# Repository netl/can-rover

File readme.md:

# can-rover

The goal is to convert cheap RC car kits in to computer driven robots by
replacing the receiver with a separate module.  
The project consists of three parts working as a whole:

1. [Hardware](#hardware)
2. [Firmware](#firmware)
3. [ROS2 node](#ros2-node)

## Hardware

features:

* XT60 passthrough
* fuse protected battery input
* battery current & voltage measurement
    * maximum rating: 20 V, 30 A
    * a charge current of 10 A max can be measured
* 2x canbus+power connectors
* 8 buffered servo channels
* 8 selectable addresses
* 8 buffered inputs with pull-up to 5V
* e-stop controlled servo power

### CAN header

Jumper for 120R termination.  
May be used to power low power stuff. Connector rated at 3 A.  

|pin|  signal |
|---|---------|
| 1 | GND     |
| 2 | Battery |
| 3 | CAN\_L  |
| 4 | CAN\_H  |

## Firmware

* can-utils: `sudo ip link set up can0 type can bitrate 500000`
* All messages are `big-endian`. 
* [python-can](https://python-can.readthedocs.io/en/stable/scripts.html) has great tools for debugging.
* build with `cd firmware; make`

### CAN messages

`base_address` is selectable by rotary switch. All messages have an offset from that address.
```c
uint8_t arbitration_id = base_address << 8; // address 0 would be: 0x000 and 7: 0x070
```

offset  |parameter       |I/O|bytes
--------|----------------|---|-----
0x0     | servo 1        | I | 1
...     | servo ...      | I | 1
0x7     | servo 8        | I | 1
0x8     | battery Voltage| O | 2
0x9     | battery Current| O | 2
0xa     | sensors 1 .. 8 | O | 1

### Servo

PWM in `1 µs` resolution and if channel hasn't been set within `1 s` it will default to `1500 µs`. For example: `servo 3` with `base_address = 5` would be set to `-90°` with:

```bash
$ cansend can0 052#3e8
```

### Battery monitor

Analog signals directly from A/D, maximum: `4095`

### Inputs

One byte where each bit represents an input

```c
bool value = inputs >> n-1 & 0x1;
```

## ROS2 node
Provided node bridges firmware to ros topics.

### Installation

1. Install [ROS2](https://docs.ros.org/en/jazzy/Installation.html)
2. create [ros2_ws](https://docs.ros.org/en/jazzy/Tutorials/Beginner-Client-Libraries/Creating-A-Workspace/Creating-A-Workspace.html)

```bash
apt install python3-rosdep python3-colcon-common-extensions
ln -s ros2_can_rover ~/ros2_ws/src/can_rover
cd ~/ros2_ws/
colcon build
source install/setup.bash
rosdep init
rosdep update
rosdep install --from-paths src -y --ignore-src
ros2 run can_rover can_rover
```

### Topics and parameters

Interfaces provided are bare minimum for simplicity

topic                      |type     |publish / subscribe|min   |max  |
---------------------------|---------|-------------------|------|-----|
`/rover/voltage`           |[Float32]|subscribe          |0   \*|20\* |
`/rover/current`           |[Float32]|subscribe          |-10 \*|30\* |
`/rover/watts`             |[Float32]|subscribe          |-200\*|600\*|
`/rover/wattHours`         |[Float32]|publish & subscribe|      |     |
`/rover/channel_<n>`       |[Float32]|publish            | -1   | 1   |
`/rover/input_<n>`         |[Bool]   |subscribe          | 0    | 1   |

*\*min/max values limited hardware tolerances and calibration*

parameter                  |type     |default   |
---------------------------|---------|----------|
`/rover/voltage_scale`     |[Float32]|20 / 2^12 |
`/rover/voltage_offset`    |[Float32]|0         |
`/rover/current_scale`     |[Float32]|-40 / 2^12|
`/rover/current_offset`    |[Float32]|10        |
`/rover/channel_<n>_scale` |[Float32]|500       |
`/rover/channel_<n>_offset`|[Float32]|1500      |

[Float32]:https://github.com/ros2/example_interfaces/blob/master/msg/Float32.msg
[Bool]:https://github.com/ros2/example_interfaces/blob/master/msg/Bool.msg

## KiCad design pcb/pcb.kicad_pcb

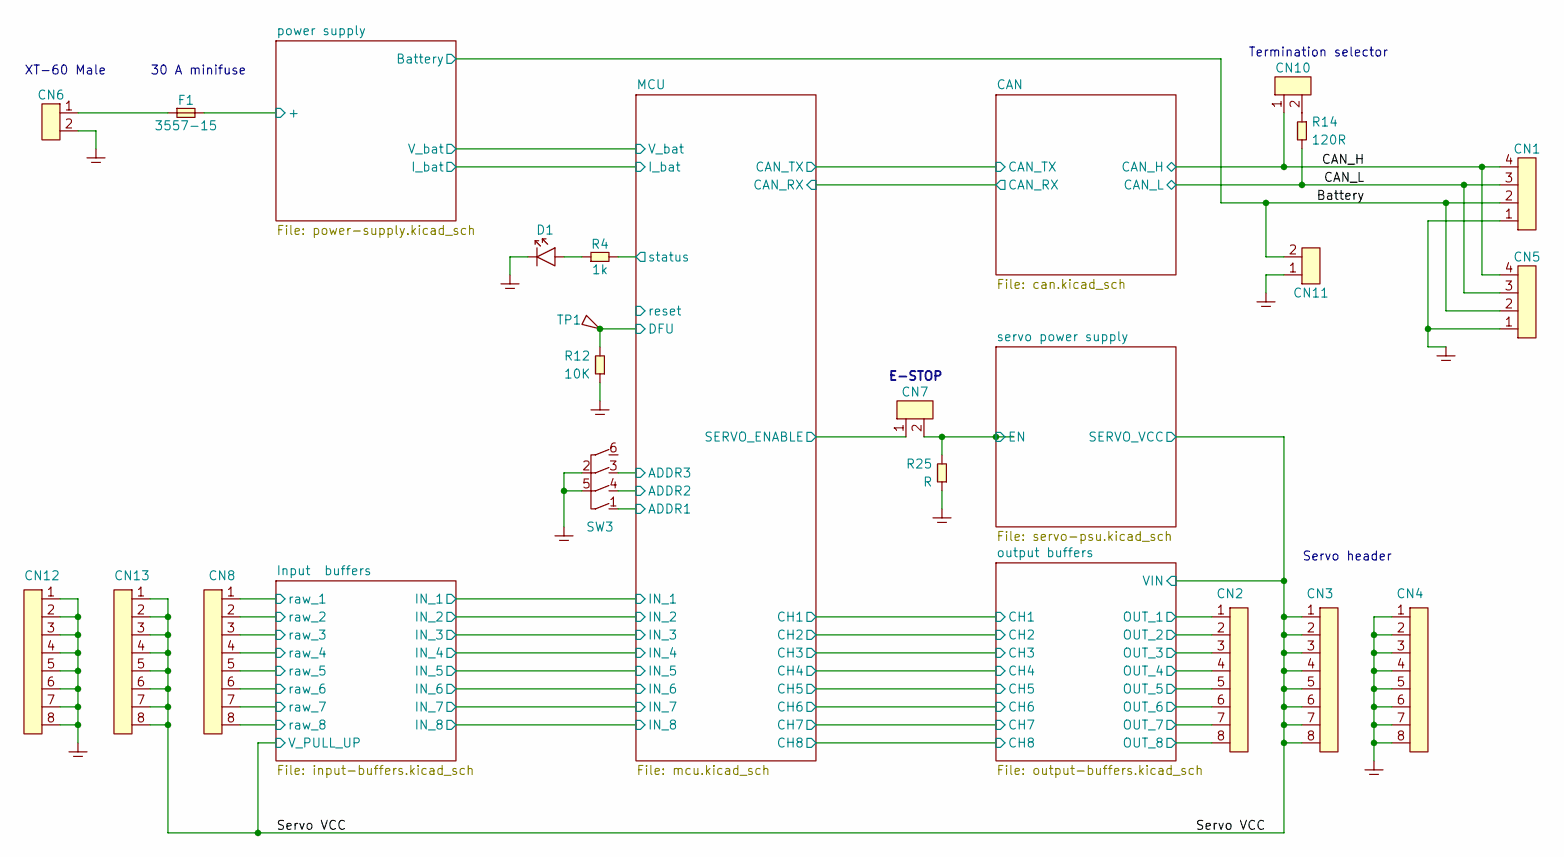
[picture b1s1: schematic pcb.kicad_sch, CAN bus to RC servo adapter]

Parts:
CN1, CN5: 1x4; jst-xh-4; MPN B4B-XH-A; DigiKey 455-B4B-XH-A-ND
CN2, CN3, CN4, CN8, CN12, CN13: 1x8
CN6, CN11: 1x2; XT60
CN7, CN10: 1x2
D1: LED; 0603
F1: F; 3557-15; MPN 3557-15; DigiKey 36-3557-15-ND
R4: 1k; 0603
R12: 10K; 0603
R14: 120R; 0603
R25: R; 0603
SW3: RD10RA8RTT; MPN RD10RA8RTT; Digi-Key 2449-RD10RA8RTT-ND
TP1: test_point

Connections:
/Battery: CN1.2, CN5.2, CN11.2; also elsewhere on the board
/CAN_H: CN1.4, CN5.4, CN10.1; also elsewhere on the board
/CAN_L: CN1.3, CN5.3, R14.2; also elsewhere on the board
/Input buffers/raw_1: CN8.1; also elsewhere on the board
/Input buffers/raw_2: CN8.2; also elsewhere on the board
/Input buffers/raw_3: CN8.3; also elsewhere on the board
/Input buffers/raw_4: CN8.4; also elsewhere on the board
/Input buffers/raw_5: CN8.5; also elsewhere on the board
/Input buffers/raw_6: CN8.6; also elsewhere on the board
/Input buffers/raw_7: CN8.7; also elsewhere on the board
/Input buffers/raw_8: CN8.8; also elsewhere on the board
/MCU/ADDR1: SW3.1; also elsewhere on the board
/MCU/ADDR2: SW3.4; also elsewhere on the board
/MCU/ADDR3: SW3.3; also elsewhere on the board
/MCU/DFU: R12.2, TP1.1 (TP); also elsewhere on the board
/MCU/SERVO_ENABLE: CN7.1; also elsewhere on the board
/MCU/status: R4.2; also elsewhere on the board
/Servo VCC: CN3.1, CN3.2, CN3.3, CN3.4, CN3.5, CN3.6, CN3.7, CN3.8, CN13.1, CN13.2, CN13.3, CN13.4, CN13.5, CN13.6, CN13.7, CN13.8; also elsewhere on the board
/output buffers/OUT_1: CN2.1; also elsewhere on the board
/output buffers/OUT_2: CN2.2; also elsewhere on the board
/output buffers/OUT_3: CN2.3; also elsewhere on the board
/output buffers/OUT_4: CN2.4; also elsewhere on the board
/output buffers/OUT_5: CN2.5; also elsewhere on the board
/output buffers/OUT_6: CN2.6; also elsewhere on the board
/output buffers/OUT_7: CN2.7; also elsewhere on the board
/output buffers/OUT_8: CN2.8; also elsewhere on the board
/power supply/+: F1.2; also elsewhere on the board
/servo power supply/EN: CN7.2, R25.2; also elsewhere on the board
GND: CN1.1, CN4.1, CN4.2, CN4.3, CN4.4, CN4.5, CN4.6, CN4.7, CN4.8, CN5.1, CN6.2, CN11.1, CN12.1, CN12.2, CN12.3, CN12.4, CN12.5, CN12.6, CN12.7, CN12.8, D1.2 (K), R12.1, R25.1, SW3.2, SW3.5; also elsewhere on the board
unnamed: CN6.1, F1.1
unnamed: CN10.2, R14.1
unnamed: D1.1 (A), R4.1

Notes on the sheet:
30 A minifuse
E-STOP
Termination selector
Servo header
XT-60 Male

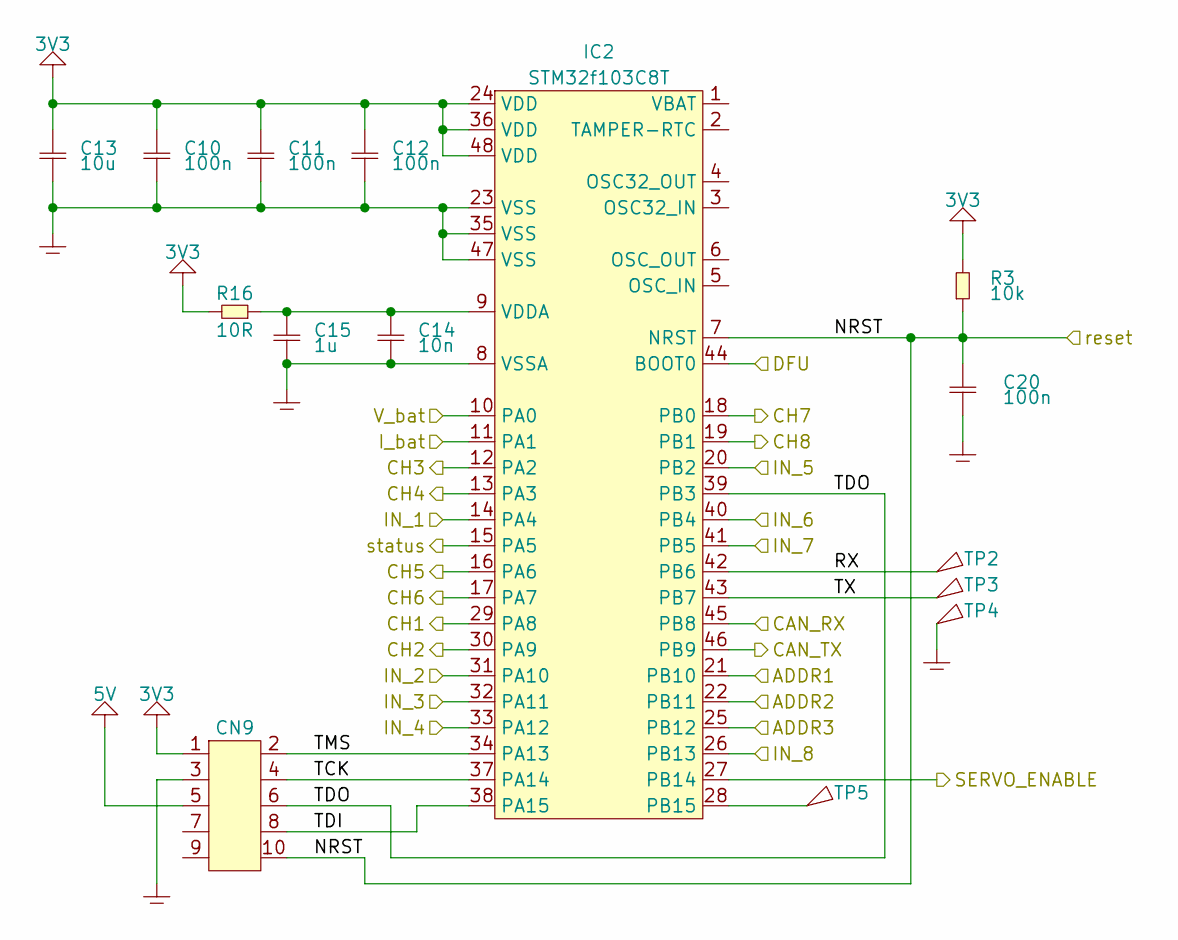
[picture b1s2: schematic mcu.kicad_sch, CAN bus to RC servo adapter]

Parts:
C10, C11, C12, C20: 100n; 0603
C13: 10u; 0603
C14: 10n; 0603
C15: 1u; 0603
CN9: 2x5; 2x5_test_points
IC2: STM32f103C8T; LQFP-48; MPN STM32F103C8T6TR; DigiKey 497-17666-1-ND
R3: 10k; 0603
R16: 10R; 0603
TP2, TP3, TP4, TP5: test_point

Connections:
3V3: C10.1, C11.1, C12.1, C13.1, CN9.1, IC2.24 (VDD), IC2.36 (VDD), IC2.48 (VDD), R3.2, R16.2; also elsewhere on the board
5V: CN9.5; also elsewhere on the board
/CAN/CAN_RX: IC2.45 (PB8); also elsewhere on the board
/CAN/CAN_TX: IC2.46 (PB9); also elsewhere on the board
/Input buffers/IN_1: IC2.14 (PA4); also elsewhere on the board
/Input buffers/IN_2: IC2.31 (PA10); also elsewhere on the board
/Input buffers/IN_3: IC2.32 (PA11); also elsewhere on the board
/Input buffers/IN_4: IC2.33 (PA12); also elsewhere on the board
/Input buffers/IN_5: IC2.20 (PB2); also elsewhere on the board
/Input buffers/IN_6: IC2.40 (PB4); also elsewhere on the board
/Input buffers/IN_7: IC2.41 (PB5); also elsewhere on the board
/Input buffers/IN_8: IC2.26 (PB13); also elsewhere on the board
/MCU/ADDR1: IC2.21 (PB10); also elsewhere on the board
/MCU/ADDR2: IC2.22 (PB11); also elsewhere on the board
/MCU/ADDR3: IC2.25 (PB12); also elsewhere on the board
/MCU/CH1: IC2.29 (PA8); also elsewhere on the board
/MCU/CH2: IC2.30 (PA9); also elsewhere on the board
/MCU/CH3: IC2.12 (PA2); also elsewhere on the board
/MCU/CH4: IC2.13 (PA3); also elsewhere on the board
/MCU/CH5: IC2.16 (PA6); also elsewhere on the board
/MCU/CH6: IC2.17 (PA7); also elsewhere on the board
/MCU/CH7: IC2.18 (PB0); also elsewhere on the board
/MCU/CH8: IC2.19 (PB1); also elsewhere on the board
/MCU/DFU: IC2.44 (BOOT0); also elsewhere on the board
/MCU/I_bat: IC2.11 (PA1); also elsewhere on the board
/MCU/NRST: C20.1, CN9.10, IC2.7 (NRST), R3.1
/MCU/RX: IC2.42 (PB6), TP2.1 (TP)
/MCU/SERVO_ENABLE: IC2.27 (PB14); also elsewhere on the board
/MCU/TCK: CN9.4, IC2.37 (PA14)
/MCU/TDI: CN9.8, IC2.38 (PA15)
/MCU/TDO: CN9.6, IC2.39 (PB3)
/MCU/TMS: CN9.2, IC2.34 (PA13)
/MCU/TX: IC2.43 (PB7), TP3.1 (TP)
/MCU/V_bat: IC2.10 (PA0); also elsewhere on the board
/MCU/status: IC2.15 (PA5); also elsewhere on the board
GND: C10.2, C11.2, C12.2, C13.2, C14.2, C15.2, C20.2, CN9.3, IC2.8 (VSSA), IC2.23 (VSS), IC2.35 (VSS), IC2.47 (VSS), TP4.1 (TP); also elsewhere on the board
unnamed: IC2.28 (PB15), TP5.1 (TP)
unnamed: C14.1, C15.1, IC2.9 (VDDA), R16.1

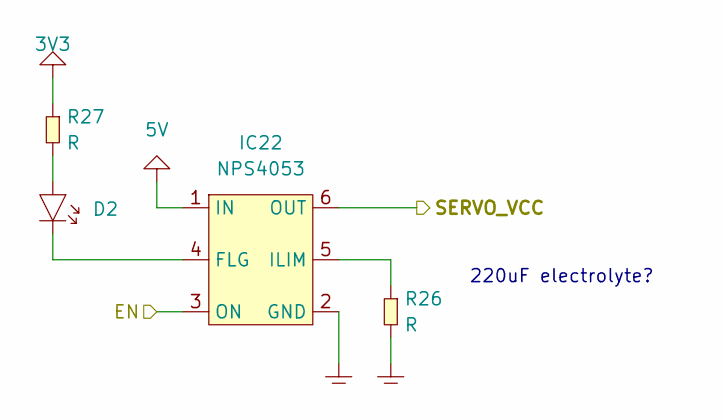
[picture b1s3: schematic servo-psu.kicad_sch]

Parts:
D2: LED; 0603
IC22: NPS4053; SOT-23-6; MPN NPS4053GVH; DigiKey 1727-NPS4053GVHCT-ND
R26, R27: R; 0603

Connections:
3V3: R27.1; also elsewhere on the board
5V: IC22.1 (IN); also elsewhere on the board
/Servo VCC: IC22.6 (OUT); also elsewhere on the board
/servo power supply/EN: IC22.3 (ON); also elsewhere on the board
GND: IC22.2 (GND), R26.2; also elsewhere on the board
unnamed: D2.1 (A), R27.2
unnamed: D2.2 (K), IC22.4 (FLG)
unnamed: IC22.5 (ILIM), R26.1

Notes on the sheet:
220uF electrolyte?

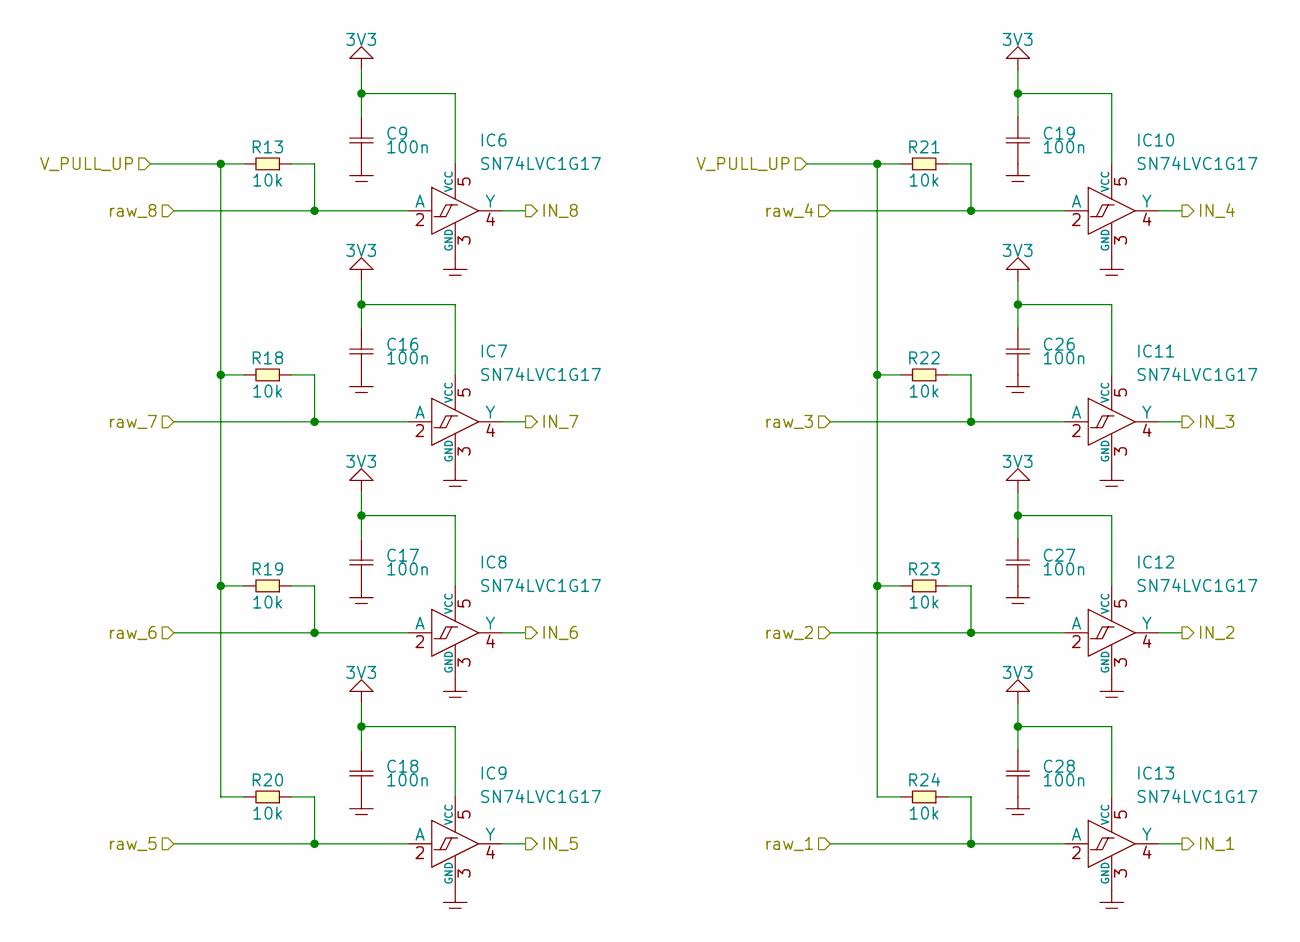
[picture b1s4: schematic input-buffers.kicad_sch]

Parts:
C9, C16, C17, C18, C19, C26, C27, C28: 100n; 0603
IC6, IC7, IC8, IC9, IC10, IC11, IC12, IC13: SN74LVC1G17; SC70-5L
R13, R18, R19, R20, R21, R22, R23, R24: 10k; 0603

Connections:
3V3: C9.2, C16.2, C17.2, C18.2, C19.2, C26.2, C27.2, C28.2, IC6.5 (VCC), IC7.5 (VCC), IC8.5 (VCC), IC9.5 (VCC), IC10.5 (VCC), IC11.5 (VCC), IC12.5 (VCC), IC13.5 (VCC); also elsewhere on the board
/Input buffers/IN_1: IC13.4 (Y); also elsewhere on the board
/Input buffers/IN_2: IC12.4 (Y); also elsewhere on the board
/Input buffers/IN_3: IC11.4 (Y); also elsewhere on the board
/Input buffers/IN_4: IC10.4 (Y); also elsewhere on the board
/Input buffers/IN_5: IC9.4 (Y); also elsewhere on the board
/Input buffers/IN_6: IC8.4 (Y); also elsewhere on the board
/Input buffers/IN_7: IC7.4 (Y); also elsewhere on the board
/Input buffers/IN_8: IC6.4 (Y); also elsewhere on the board
/Input buffers/raw_1: IC13.2 (A), R24.1; also elsewhere on the board
/Input buffers/raw_2: IC12.2 (A), R23.1; also elsewhere on the board
/Input buffers/raw_3: IC11.2 (A), R22.1; also elsewhere on the board
/Input buffers/raw_4: IC10.2 (A), R21.1; also elsewhere on the board
/Input buffers/raw_5: IC9.2 (A), R20.1; also elsewhere on the board
/Input buffers/raw_6: IC8.2 (A), R19.1; also elsewhere on the board
/Input buffers/raw_7: IC7.2 (A), R18.1; also elsewhere on the board
/Input buffers/raw_8: IC6.2 (A), R13.1; also elsewhere on the board
/Servo VCC: R13.2, R18.2, R19.2, R20.2, R21.2, R22.2, R23.2, R24.2; also elsewhere on the board
GND: C9.1, C16.1, C17.1, C18.1, C19.1, C26.1, C27.1, C28.1, IC6.3 (GND), IC7.3 (GND), IC8.3 (GND), IC9.3 (GND), IC10.3 (GND), IC11.3 (GND), IC12.3 (GND), IC13.3 (GND); also elsewhere on the board

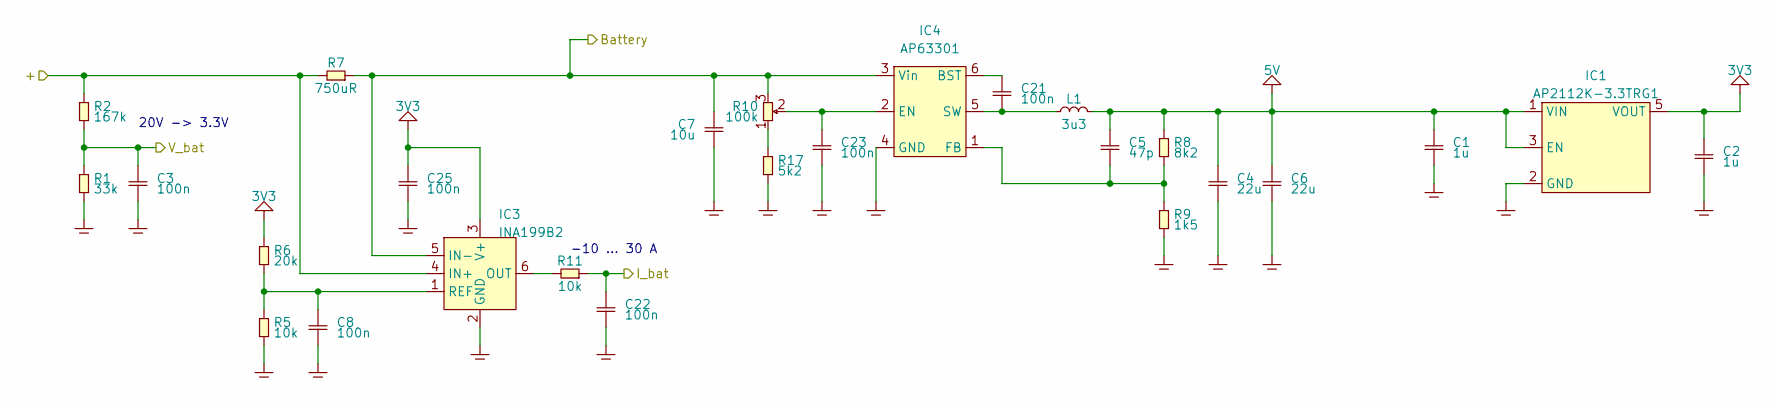
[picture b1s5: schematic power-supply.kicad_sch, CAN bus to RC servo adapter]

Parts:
C1, C2: 1u; 0603
C3, C8, C21, C22, C23, C25: 100n; 0603
C4, C6: 22u; 0603
C5: 47p; 0603
C7: 10u; 0603
IC1: AP2112K-3.3TRG1; SOT-23-5; MPN AP2112K-3.3TRG1; Digi-Key AP2112K-3.3TRG1DICT-ND
IC3: INA199B2; SC70-6L; MPN INA199B2DCKR; DigiKey 296-40119-1-ND
IC4: AP63301; TSOT-26; MPN AP63301WU-7; DigiKey 31-AP63301WU-7CT-ND
L1: 3u3; 5x5; MPN VLS5045EX-3R3N; DigiKey 445-174398-1-ND
R1: 33k; 0603
R2: 167k; 0603
R5, R11: 10k; 0603
R6: 20k; 0603
R7: 750uR; 2512-high-current
R8: 8k2; 0603
R9: 1k5; 0603
R10: 100k; 3362P; MPN 3362P-1-104LF; DigiKey 3362P-104LF-ND
R17: 5k2; 0603

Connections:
3V3: C2.1, C25.1, IC1.5 (VOUT), IC3.3 (V+), R6.2; also elsewhere on the board
5V: C1.1, C4.1, C5.1, C6.1, IC1.1 (VIN), IC1.3 (EN), L1.2, R8.2; also elsewhere on the board
/Battery: C7.1, IC3.5 (IN-), IC4.3 (Vin), R7.1, R10.3; also elsewhere on the board
/MCU/I_bat: C22.1, R11.1; also elsewhere on the board
/MCU/V_bat: C3.1, R1.2, R2.1; also elsewhere on the board
/power supply/+: IC3.4 (IN+), R2.2, R7.2; also elsewhere on the board
GND: C1.2, C2.2, C3.2, C4.2, C6.2, C7.2, C8.2, C22.2, C23.2, C25.2, IC1.2 (GND), IC3.2 (GND), IC4.4 (GND), R1.1, R5.1, R9.1, R17.1; also elsewhere on the board
unnamed: IC3.6 (OUT), R11.2
unnamed: C8.1, IC3.1 (REF), R5.2, R6.1
unnamed: C21.1, IC4.6 (BST)
unnamed: C23.1, IC4.2 (EN), R10.2
unnamed: C5.2, IC4.1 (FB), R8.1, R9.2
unnamed: C21.2, IC4.5 (SW), L1.1
unnamed: R10.1, R17.2

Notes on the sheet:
-10 ... 30 A
20V -> 3.3V

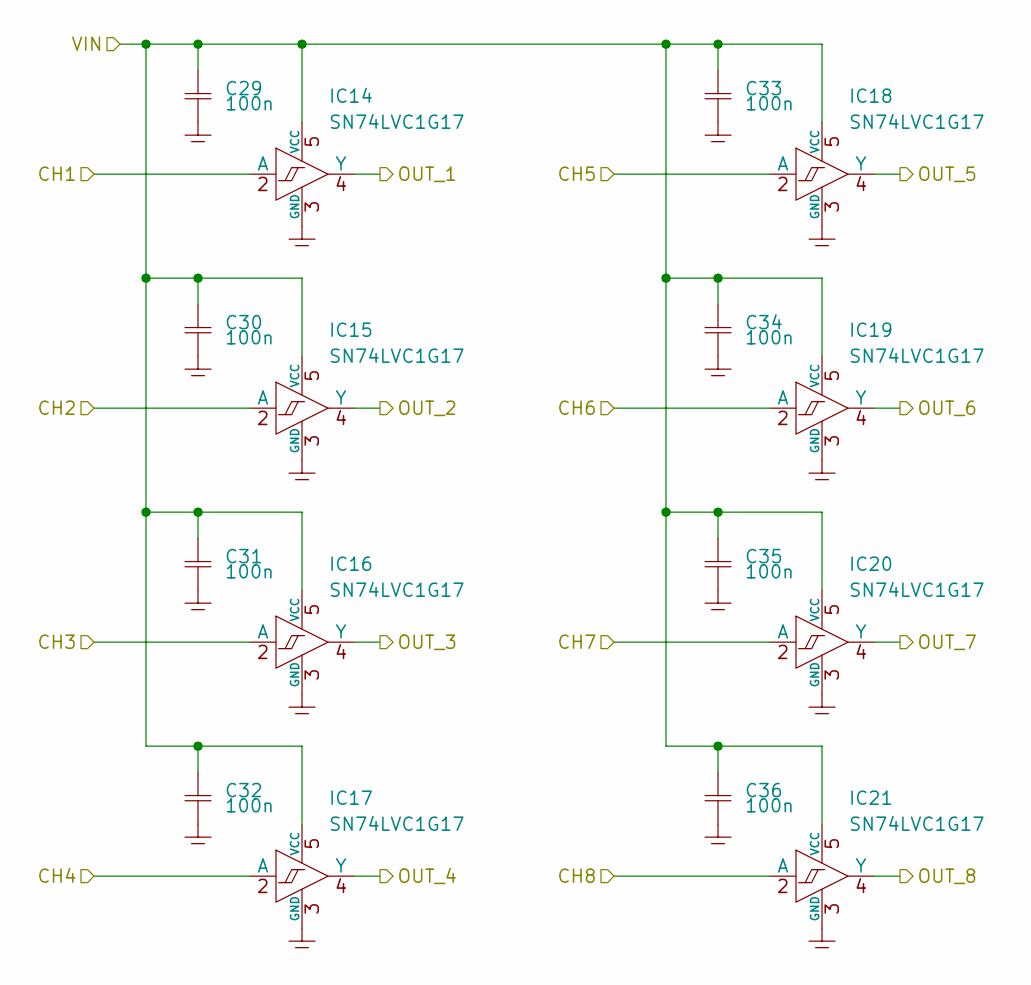
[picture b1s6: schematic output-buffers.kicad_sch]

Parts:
C29, C30, C31, C32, C33, C34, C35, C36: 100n; 0603
IC14, IC15, IC16, IC17, IC18, IC19, IC20, IC21: SN74LVC1G17; SC70-5L

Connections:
/MCU/CH1: IC14.2 (A); also elsewhere on the board
/MCU/CH2: IC15.2 (A); also elsewhere on the board
/MCU/CH3: IC16.2 (A); also elsewhere on the board
/MCU/CH4: IC17.2 (A); also elsewhere on the board
/MCU/CH5: IC18.2 (A); also elsewhere on the board
/MCU/CH6: IC19.2 (A); also elsewhere on the board
/MCU/CH7: IC20.2 (A); also elsewhere on the board
/MCU/CH8: IC21.2 (A); also elsewhere on the board
/Servo VCC: C29.2, C30.2, C31.2, C32.2, C33.2, C34.2, C35.2, C36.2, IC14.5 (VCC), IC15.5 (VCC), IC16.5 (VCC), IC17.5 (VCC), IC18.5 (VCC), IC19.5 (VCC), IC20.5 (VCC), IC21.5 (VCC); also elsewhere on the board
/output buffers/OUT_1: IC14.4 (Y); also elsewhere on the board
/output buffers/OUT_2: IC15.4 (Y); also elsewhere on the board
/output buffers/OUT_3: IC16.4 (Y); also elsewhere on the board
/output buffers/OUT_4: IC17.4 (Y); also elsewhere on the board
/output buffers/OUT_5: IC18.4 (Y); also elsewhere on the board
/output buffers/OUT_6: IC19.4 (Y); also elsewhere on the board
/output buffers/OUT_7: IC20.4 (Y); also elsewhere on the board
/output buffers/OUT_8: IC21.4 (Y); also elsewhere on the board
GND: C29.1, C30.1, C31.1, C32.1, C33.1, C34.1, C35.1, C36.1, IC14.3 (GND), IC15.3 (GND), IC16.3 (GND), IC17.3 (GND), IC18.3 (GND), IC19.3 (GND), IC20.3 (GND), IC21.3 (GND); also elsewhere on the board

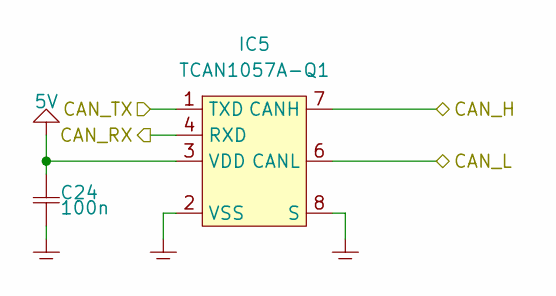
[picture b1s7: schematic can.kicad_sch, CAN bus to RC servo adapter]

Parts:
C24: 100n; 0603
IC5: TCAN1057A-Q1; TSOT-23-8; MPN TCAN1057AVDDFRQ1; DigiKey 296-TCAN1057AVDDFRQ1CT-ND

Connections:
5V: C24.1, IC5.3 (VDD); also elsewhere on the board
/CAN/CAN_RX: IC5.4 (RXD); also elsewhere on the board
/CAN/CAN_TX: IC5.1 (TXD); also elsewhere on the board
/CAN_H: IC5.7 (CANH); also elsewhere on the board
/CAN_L: IC5.6 (CANL); also elsewhere on the board
GND: C24.2, IC5.2 (VSS), IC5.8 (S); also elsewhere on the board

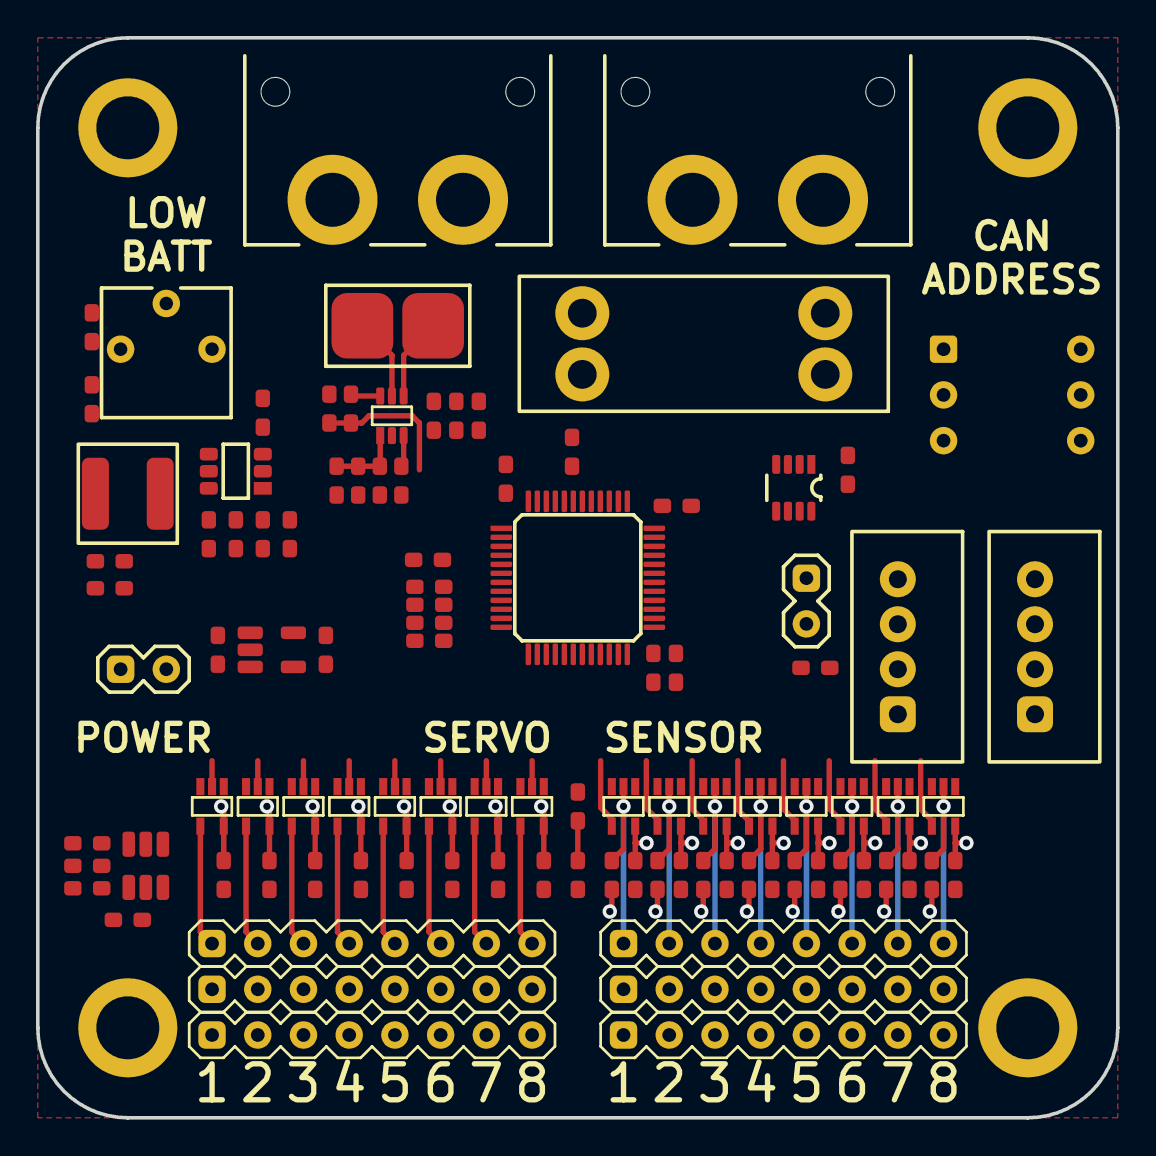
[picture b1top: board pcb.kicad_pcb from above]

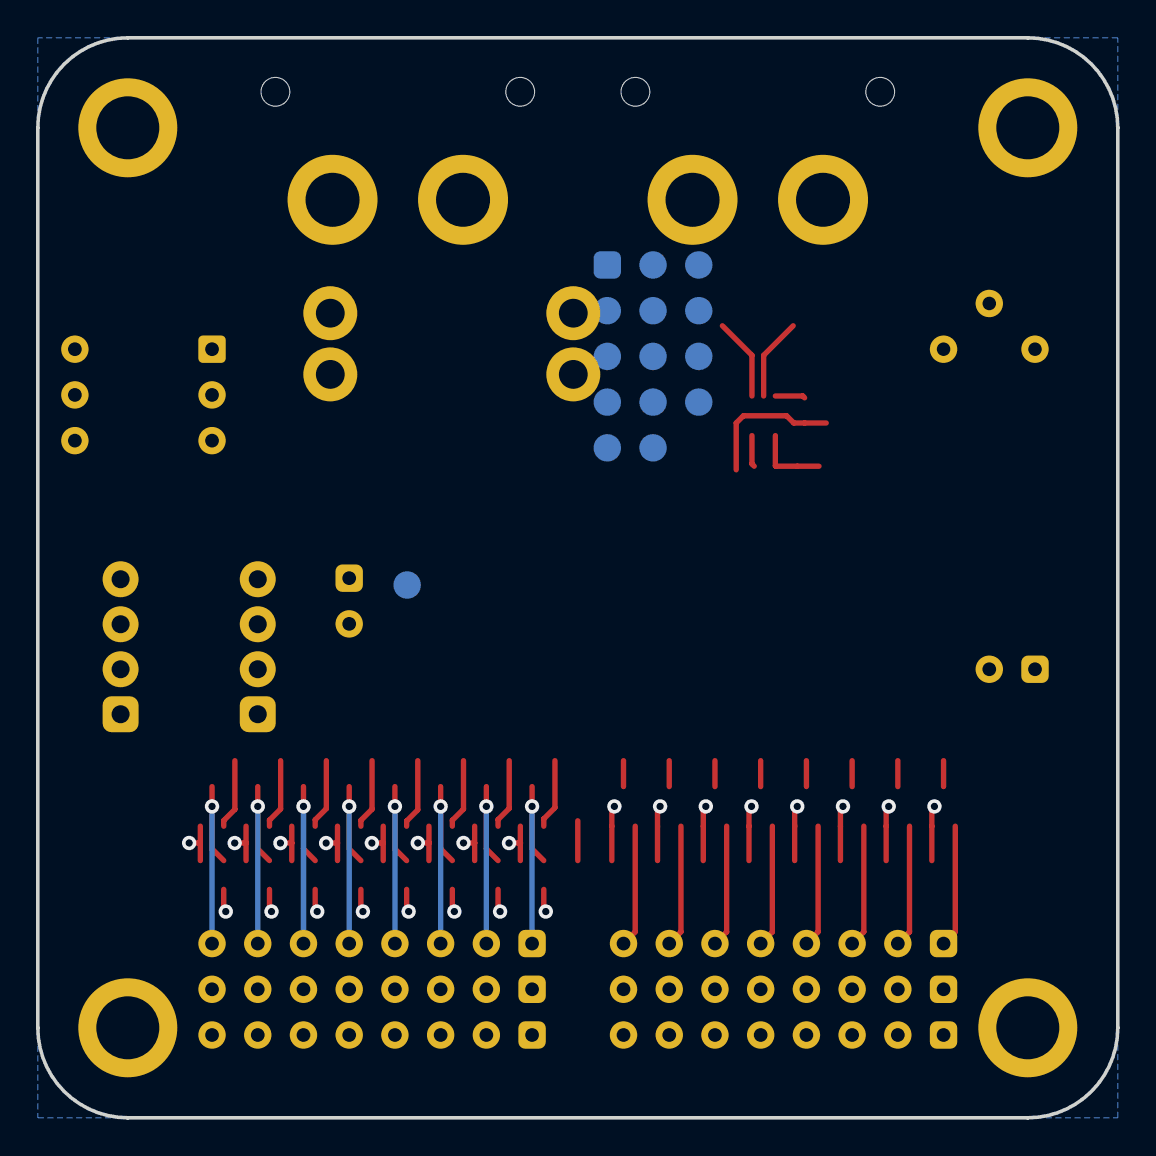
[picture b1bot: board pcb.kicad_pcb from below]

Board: 4 copper layers, 60.0 x 60.0 mm, 107 parts (6 on the bottom side), 73 nets.

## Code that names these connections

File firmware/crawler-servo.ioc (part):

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Mcu.Name=STM32F103C(8-B)Tx
Mcu.Package=LQFP48
Mcu.UserName=STM32F103C8Tx
PA0-WKUP.Signal=ADCx_IN0
PA1.Signal=ADCx_IN1
PA10.GPIOParameters=GPIO_Label
PA10.GPIO_Label=IN_2
PA10.Signal=GPIO_Input
PA11.GPIOParameters=GPIO_Label
PA11.GPIO_Label=IN_3
PA11.Signal=GPIO_Input
PA12.GPIOParameters=GPIO_Label
PA12.GPIO_Label=IN_4
PA12.Signal=GPIO_Input
PA2.Signal=S_TIM2_CH3
PA3.Signal=S_TIM2_CH4
PA4.GPIOParameters=GPIO_Label
PA4.GPIO_Label=IN_1
PA4.Signal=GPIO_Input
PA5.GPIOParameters=GPIO_Label
PA5.GPIO_Label=status
PA5.Signal=GPIO_Output
PA6.Signal=S_TIM3_CH1
PA7.Signal=S_TIM3_CH2
PA8.Signal=S_TIM1_CH1
PA9.Signal=S_TIM1_CH2
PB0.Signal=S_TIM3_CH3
PB1.Signal=S_TIM3_CH4
PB10.GPIOParameters=GPIO_PuPd,GPIO_Label
PB10.GPIO_Label=ADDR_1
PB10.GPIO_PuPd=GPIO_PULLUP
PB10.Signal=GPIO_Input
PB11.GPIOParameters=GPIO_PuPd,GPIO_Label
PB11.GPIO_Label=ADDR_2
PB11.GPIO_PuPd=GPIO_PULLUP
PB11.Signal=GPIO_Input
PB12.GPIOParameters=GPIO_PuPd,GPIO_Label
PB12.GPIO_Label=ADDR_3
PB12.GPIO_PuPd=GPIO_PULLUP
PB12.Signal=GPIO_Input
PB13.GPIOParameters=GPIO_Label
PB13.GPIO_Label=IN_8
PB13.Signal=GPIO_Input
PB2.GPIOParameters=GPIO_Label
PB2.GPIO_Label=IN_5
PB2.Signal=GPIO_Input
PB4.GPIOParameters=GPIO_Label
PB4.GPIO_Label=IN_6
PB4.Signal=GPIO_Input
PB5.GPIOParameters=GPIO_Label
PB5.GPIO_Label=IN_7
PB5.Signal=GPIO_Input
PB8.Mode=CAN_Activate
PB8.Signal=CAN_RX
PB9.Mode=CAN_Activate
PB9.Signal=CAN_TX
RCC.SYSCLKFreq_VALUE=24000000
RCC.SYSCLKSource=RCC_SYSCLKSOURCE_PLLCLK
board=custom

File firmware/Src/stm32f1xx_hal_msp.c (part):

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
    __HAL_RCC_GPIOA_CLK_ENABLE();
    /**ADC1 GPIO Configuration
    PA0-WKUP     ------> ADC1_IN0
    PA1     ------> ADC1_IN1
    */
    GPIO_InitStruct.Pin = GPIO_PIN_0|GPIO_PIN_1;
    GPIO_InitStruct.Mode = GPIO_MODE_ANALOG;
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    __HAL_RCC_ADC1_CLK_DISABLE();

    /**ADC1 GPIO Configuration
    PA0-WKUP     ------> ADC1_IN0
    PA1     ------> ADC1_IN1
    */
    HAL_GPIO_DeInit(GPIOA, GPIO_PIN_0|GPIO_PIN_1);

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
    __HAL_RCC_GPIOB_CLK_ENABLE();
    /**CAN GPIO Configuration
    PB8     ------> CAN_RX
    PB9     ------> CAN_TX
    */
    GPIO_InitStruct.Pin = GPIO_PIN_8;
    GPIO_InitStruct.Mode = GPIO_MODE_INPUT;
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    __HAL_RCC_CAN1_CLK_DISABLE();

    /**CAN GPIO Configuration
    PB8     ------> CAN_RX
    PB9     ------> CAN_TX
    */
    HAL_GPIO_DeInit(GPIOB, GPIO_PIN_8|GPIO_PIN_9);

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  /* USER CODE END TIM1_MspPostInit 0 */
    __HAL_RCC_GPIOA_CLK_ENABLE();
    /**TIM1 GPIO Configuration
    PA8     ------> TIM1_CH1
    PA9     ------> TIM1_CH2
    */
    GPIO_InitStruct.Pin = GPIO_PIN_8|GPIO_PIN_9;
    GPIO_InitStruct.Mode = GPIO_MODE_AF_PP;
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
    __HAL_RCC_GPIOA_CLK_ENABLE();
    /**TIM2 GPIO Configuration
    PA2     ------> TIM2_CH3
    PA3     ------> TIM2_CH4
    */
    GPIO_InitStruct.Pin = GPIO_PIN_2|GPIO_PIN_3;
    GPIO_InitStruct.Mode = GPIO_MODE_AF_PP;
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    __HAL_RCC_GPIOA_CLK_ENABLE();
    __HAL_RCC_GPIOB_CLK_ENABLE();
    /**TIM3 GPIO Configuration
    PA6     ------> TIM3_CH1
    PA7     ------> TIM3_CH2
    PB0     ------> TIM3_CH3
    PB1     ------> TIM3_CH4
    */
    GPIO_InitStruct.Pin = GPIO_PIN_6|GPIO_PIN_7;
    GPIO_InitStruct.Mode = GPIO_MODE_AF_PP;
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
    __HAL_RCC_GPIOB_CLK_ENABLE();
    /**USART1 GPIO Configuration
    PB6     ------> USART1_TX
    PB7     ------> USART1_RX
    */
    GPIO_InitStruct.Pin = GPIO_PIN_6;
    GPIO_InitStruct.Mode = GPIO_MODE_AF_PP;
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    __HAL_RCC_USART1_CLK_DISABLE();

    /**USART1 GPIO Configuration
    PB6     ------> USART1_TX
    PB7     ------> USART1_RX
    */
    HAL_GPIO_DeInit(GPIOB, GPIO_PIN_6|GPIO_PIN_7);

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
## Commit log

2023-08-31 created stm32cubemx project
2023-09-19 changed can baudrate
2023-09-26 pwm now works at 50 hz for some reason
2023-09-28 fixed pwm configuration. ch1 now goes to servo middle
2023-10-24 added instructions for gdb
2023-10-31 added command for setting up canbus
2023-10-31 added jlink command
2023-12-06 created schematic
2023-12-07 continued work on schematic
2023-12-27 changed mcu layout to allow all desired features. added stm32 to schematic
2023-12-29 enabled canbus interrupt
2023-12-29 changed gdb commands
2023-12-29 tweaked gdb commands more. windows "broke" the makefile.....
2024-01-14 schematic mostly done
2024-01-14 created schematic pdf
2024-01-22 started work on layout
2024-01-22 cleaned up project root
2024-01-24 canbus seems to work both ways now
2024-01-25 canbus now changes servo pwm
2024-01-29 adc value now being sent over canbus
2024-02-21 got multiple channels to work somehow. tried to add blinking to error handler
2024-02-22 changed servo pwm prescaler so that the whole range should be within 2000
2024-02-27 changed prescale back to 3, set channels to range limits
2024-02-28 changed servo timings and communication to be microseconds instead of something arbitrary
2024-02-28 updated documentation
2024-03-26 fixed 5V being GND net
2024-04-24 removed FTDI and SBUS headers for now
2024-04-24 added can+pwr header, worked layout
2024-04-25 added DIP switches, footprints
2024-05-01 updated components. worked on layout
2024-05-03 added missing footprints
2024-05-07 worked on layout
2024-05-16 worked on layout. changed JTAG pinout and changed it to bottomside test-points
2024-05-20 removed RTC crystal, started routing
2024-05-21 routing completed
2024-05-21 updated pcb documentation
2024-05-28 added resistor to tweak step-down low-voltage range. flipped trimmer polarity
2024-05-29 minor tweaks on battery current paths
2024-06-05 servo control now resets to middle if they aren't updated often enough
2024-07-02 circuit seems to kill buck module at 14 V. even when installed as a dead bug
2024-07-16 changed current measurement offset resistor values
2024-08-06 updated component values
2024-08-14 swapped devboard to first version PCB. CAN doesn't send/receive properly
2024-08-15 rebuilt cubemx project and canbus works now
2024-08-15 cleanup, address dip switches now work, both ADC results are sent over CAN
2024-08-27 changed output connector to xt60 & 2x jst-xh-4
2024-09-17 fixed can packet length to 2 and can ID filtering
2024-09-18 added ros2 node
2024-09-25 renamed ros node, was easier to delete and copy fixed code from elsewhere
2024-09-25 removed old ros2 node
2024-09-26 rewrote readme
2024-09-26 renamed node. changed channel numbering from 0-7 to 1-8 to match the pcb
2024-09-26 added gitignore
2024-10-15 added kicad backups to gitignore
2024-10-22 worked on pinout
2024-10-23 wattHours can now be set, no need to clamp to zero
2024-10-23 deleted swap file
2024-10-29 added hierarchial sheets for buffering
2024-10-29 updated gitignore
2024-10-29 updated schematic pdf
2024-11-19 added buffer
2024-12-17 cleaned up buffer hierarchy
2025-01-21 added power switch for servos
2025-02-25 worked on layout. changed step-down module
2025-02-26 documentation, dependencies updated
2025-03-21 updated xt60 footprint
2025-03-28 fixed reversed sensor signals
2025-04-08 changed CAN driver
2025-04-22 changed dip switch to rotary type
2025-05-27 worked on layout, added power to sensor connectors

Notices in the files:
firmware/Src/stm32f1xx_hal_msp.c:
Copyright (c) 2023 STMicroelectronics.
All rights reserved.
This software is licensed under terms that can be found in the LICENSE file
